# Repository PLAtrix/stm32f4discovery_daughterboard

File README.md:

This is a Daughterboard for the STM32F4 Discovery for Paparazzi.
Mainly a brakout board for all bus (UART, SPI, I2C...) and PWM outputs.

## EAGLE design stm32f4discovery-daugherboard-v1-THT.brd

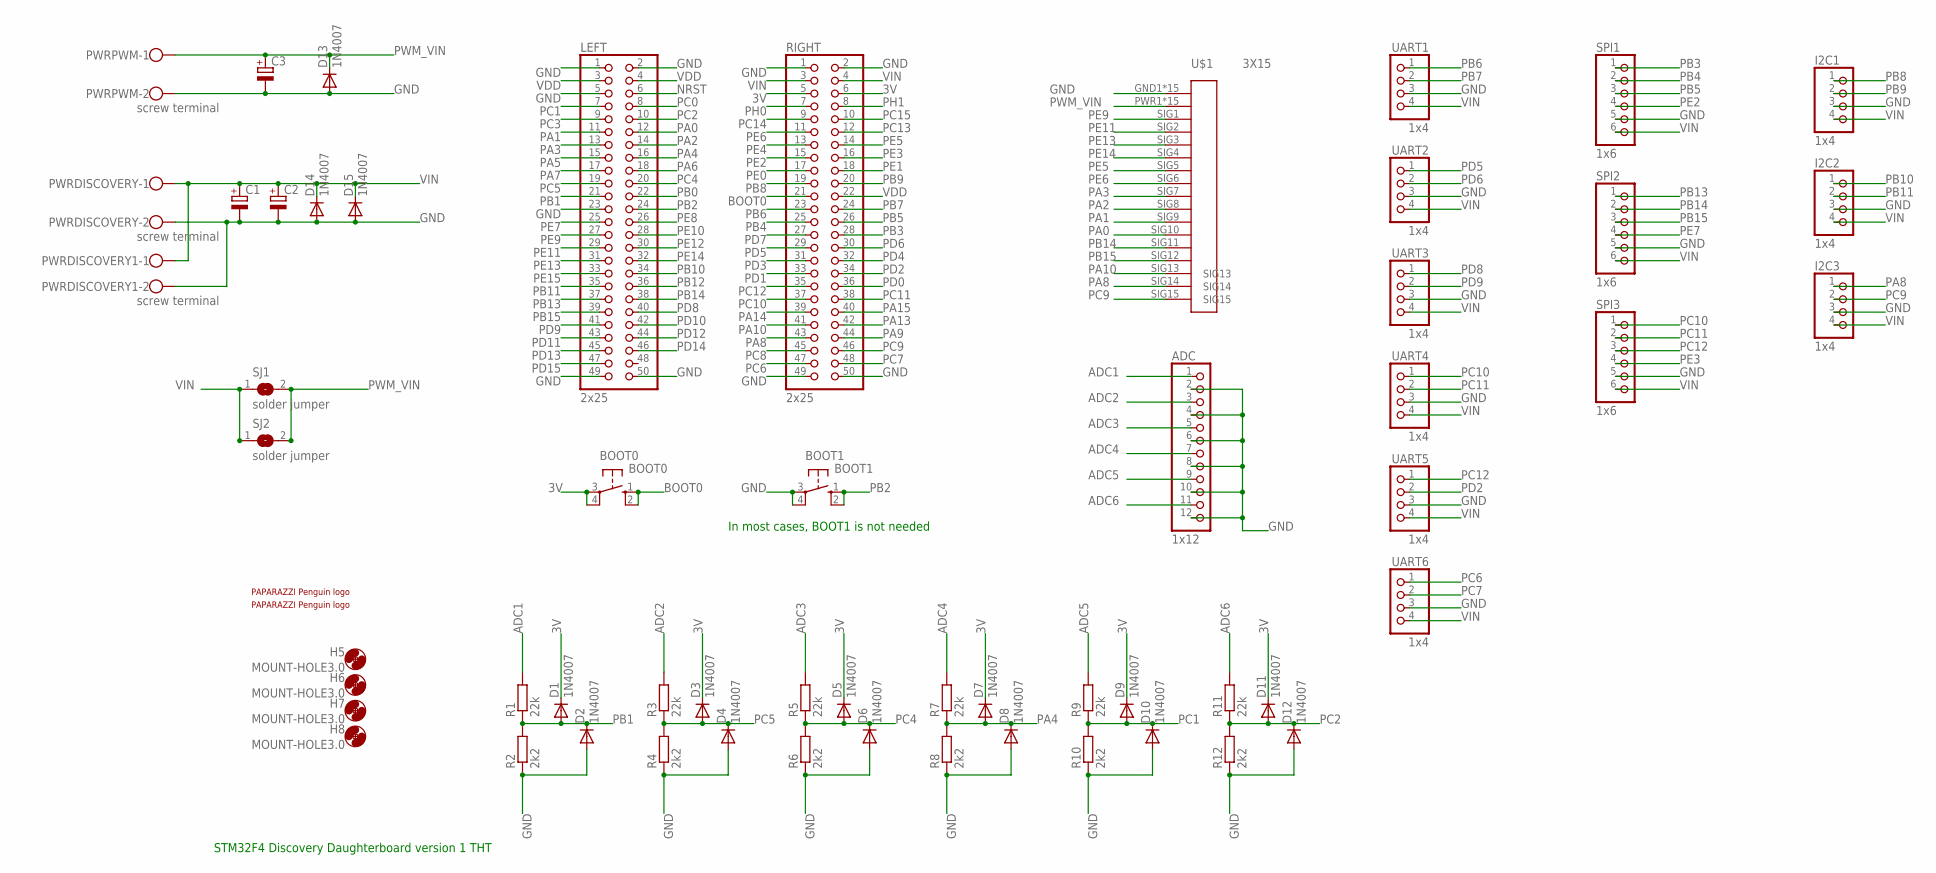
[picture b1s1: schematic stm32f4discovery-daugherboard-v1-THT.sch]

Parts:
ADC: 1x12; 1X12/90
BOOT0: BOOT0; B3F-10XX
BOOT1: BOOT1; B3F-10XX
C1, C2, C3: CPOL-EUE5-8.5; E5-8,5
D1, D2, D3, D4, D5, D6, D7, D8, D9, D10, D11, D12, D13, D14, D15: 1N4007; DO41-7.6_2
H5, H6, H7, H8: MOUNT-HOLE3.0; 3,0
I2C1, I2C2, I2C3: 1x4; 1X04/90
LEFT: 2x25; 2X25
PWRDISCOVERY: screw terminal; W237-102
PWRDISCOVERY1: screw terminal; W237-102; MPN 237-102
PWRPWM: screw terminal; W237-102
R1, R3, R5, R7, R9, R11: 22k; 0204/7
R2, R4, R6, R8, R10, R12: 2k2; 0204/7
RIGHT: 2x25; 2X25
SJ1, SJ2: solder jumper; SJW
SPI1, SPI2, SPI3: 1x6; 1X06/90
U$1: 3X15
U$2: PAPARAZZI
U$4: üAüARAZZI_1400; PAPARAZZI_1400
UART1, UART2, UART3, UART4, UART5, UART6: 1x4; 1X04/90

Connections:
3V: BOOT0.3, BOOT0.4 (P1), D1.C, D3.C, D5.C, D7.C, D9.C, D11.C, RIGHT.5, RIGHT.6
ADC1: ADC.1, R1.2
ADC2: ADC.3, R3.2
ADC3: ADC.5, R5.2
ADC4: ADC.7, R7.2
ADC5: ADC.9, R9.2
ADC6: ADC.11, R11.2
BOOT0: BOOT0.1 (S), BOOT0.2 (S1), RIGHT.21
GND: ADC.2, ADC.4, ADC.6, ADC.8, ADC.10, ADC.12, BOOT1.3, BOOT1.4 (P1), C1.-, C2.-, C3.-, D2.A, D4.A, D6.A, D8.A, D10.A, D12.A, D13.A, D14.A, D15.A, I2C1.3, I2C2.3, I2C3.3, LEFT.1, LEFT.2, LEFT.5, LEFT.23, LEFT.49, LEFT.50, PWRDISCOVERY.2, PWRDISCOVERY1.2, PWRPWM.2, R2.1, R4.1, R6.1, R8.1, R10.1, R12.1, RIGHT.1, RIGHT.2, RIGHT.49, RIGHT.50, SPI1.5, SPI2.5, SPI3.5, U$1.GND1 (GND), U$1.GND2 (GND), U$1.GND3 (GND), U$1.GND4 (GND), U$1.GND5 (GND), U$1.GND6 (GND), U$1.GND7 (GND), U$1.GND8 (GND), U$1.GND9 (GND), U$1.GND10 (GND), U$1.GND11 (GND), U$1.GND12 (GND), U$1.GND13 (GND), U$1.GND14 (GND), U$1.GND15 (GND), UART1.3, UART2.3, UART3.3, UART4.3, UART5.3, UART6.3
NRST: LEFT.6
PA0: LEFT.12, U$1.SIG10
PA1: LEFT.11, U$1.SIG9
PA2: LEFT.14, U$1.SIG8
PA3: LEFT.13, U$1.SIG7
PA4: D7.A, D8.C, LEFT.16, R7.1, R8.2
PA5: LEFT.15
PA6: LEFT.18
PA7: LEFT.17
PA8: I2C3.1, RIGHT.43, U$1.SIG14
PA9: RIGHT.44
PA10: RIGHT.41, U$1.SIG13
PA13: RIGHT.42
PA14: RIGHT.39
PA15: RIGHT.40
PB0: LEFT.22
PB1: D1.A, D2.C, LEFT.21, R1.1, R2.2
PB2: BOOT1.1 (S), BOOT1.2 (S1), LEFT.24
PB3: RIGHT.28, SPI1.1
PB4: RIGHT.25, SPI1.2
PB5: RIGHT.26, SPI1.3
PB6: RIGHT.23, UART1.1
PB7: RIGHT.24, UART1.2
PB8: I2C1.1, RIGHT.19
PB9: I2C1.2, RIGHT.20
PB10: I2C2.1, LEFT.34
PB11: I2C2.2, LEFT.35
PB12: LEFT.36
PB13: LEFT.37, SPI2.1
PB14: LEFT.38, SPI2.2, U$1.SIG11
PB15: LEFT.39, SPI2.3, U$1.SIG12
PC0: LEFT.8
PC1: D9.A, D10.C, LEFT.7, R9.1, R10.2
PC2: D11.A, D12.C, LEFT.10, R11.1, R12.2
PC3: LEFT.9
PC4: D5.A, D6.C, LEFT.20, R5.1, R6.2
PC5: D3.A, D4.C, LEFT.19, R3.1, R4.2
PC6: RIGHT.47, UART6.1
PC7: RIGHT.48, UART6.2
PC8: RIGHT.45
PC9: I2C3.2, RIGHT.46, U$1.SIG15
PC10: RIGHT.37, SPI3.1, UART4.1
PC11: RIGHT.38, SPI3.2, UART4.2
PC12: RIGHT.35, SPI3.3, UART5.1
PC13: RIGHT.12
PC14: RIGHT.9
PC15: RIGHT.10
PD0: RIGHT.36
PD1: RIGHT.33
PD2: RIGHT.34, UART5.2
PD3: RIGHT.31
PD4: RIGHT.32
PD5: RIGHT.29, UART2.1
PD6: RIGHT.30, UART2.2
PD7: RIGHT.27
PD8: LEFT.40, UART3.1
PD9: LEFT.41, UART3.2
PD10: LEFT.42
PD11: LEFT.43
PD12: LEFT.44
PD13: LEFT.45
PD14: LEFT.46
PD15: LEFT.47
PE0: RIGHT.17
PE1: RIGHT.18
PE2: RIGHT.15, SPI1.4
PE3: RIGHT.16, SPI3.4
PE4: RIGHT.13
PE5: RIGHT.14, U$1.SIG5
PE6: RIGHT.11, U$1.SIG6
PE7: LEFT.25, SPI2.4
PE8: LEFT.26
PE9: LEFT.27, U$1.SIG1
PE10: LEFT.28
PE11: LEFT.29, U$1.SIG2
PE12: LEFT.30
PE13: LEFT.31, U$1.SIG3
PE14: LEFT.32, U$1.SIG4
PE15: LEFT.33
PH0: RIGHT.7
PH1: RIGHT.8
PWM_VIN: C3.+, D13.C, PWRPWM.1, SJ1.2, SJ2.2, U$1.PWR1 (PWR), U$1.PWR2 (PWR), U$1.PWR3 (PWR), U$1.PWR4 (PWR), U$1.PWR5 (PWR), U$1.PWR6 (PWR), U$1.PWR7 (PWR), U$1.PWR8 (PWR), U$1.PWR9 (PWR), U$1.PWR10 (PWR), U$1.PWR11 (PWR), U$1.PWR12 (PWR), U$1.PWR13 (PWR), U$1.PWR14 (PWR), U$1.PWR15 (PWR)
VDD: LEFT.3, LEFT.4, RIGHT.22
VIN: C1.+, C2.+, D14.C, D15.C, I2C1.4, I2C2.4, I2C3.4, PWRDISCOVERY.1, PWRDISCOVERY1.1, RIGHT.3, RIGHT.4, SJ1.1, SJ2.1, SPI1.6, SPI2.6, SPI3.6, UART1.4, UART2.4, UART3.4, UART4.4, UART5.4, UART6.4

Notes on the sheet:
STM32F4 Discovery Daughterboard version 1 THT
In most cases, BOOT1 is not needed

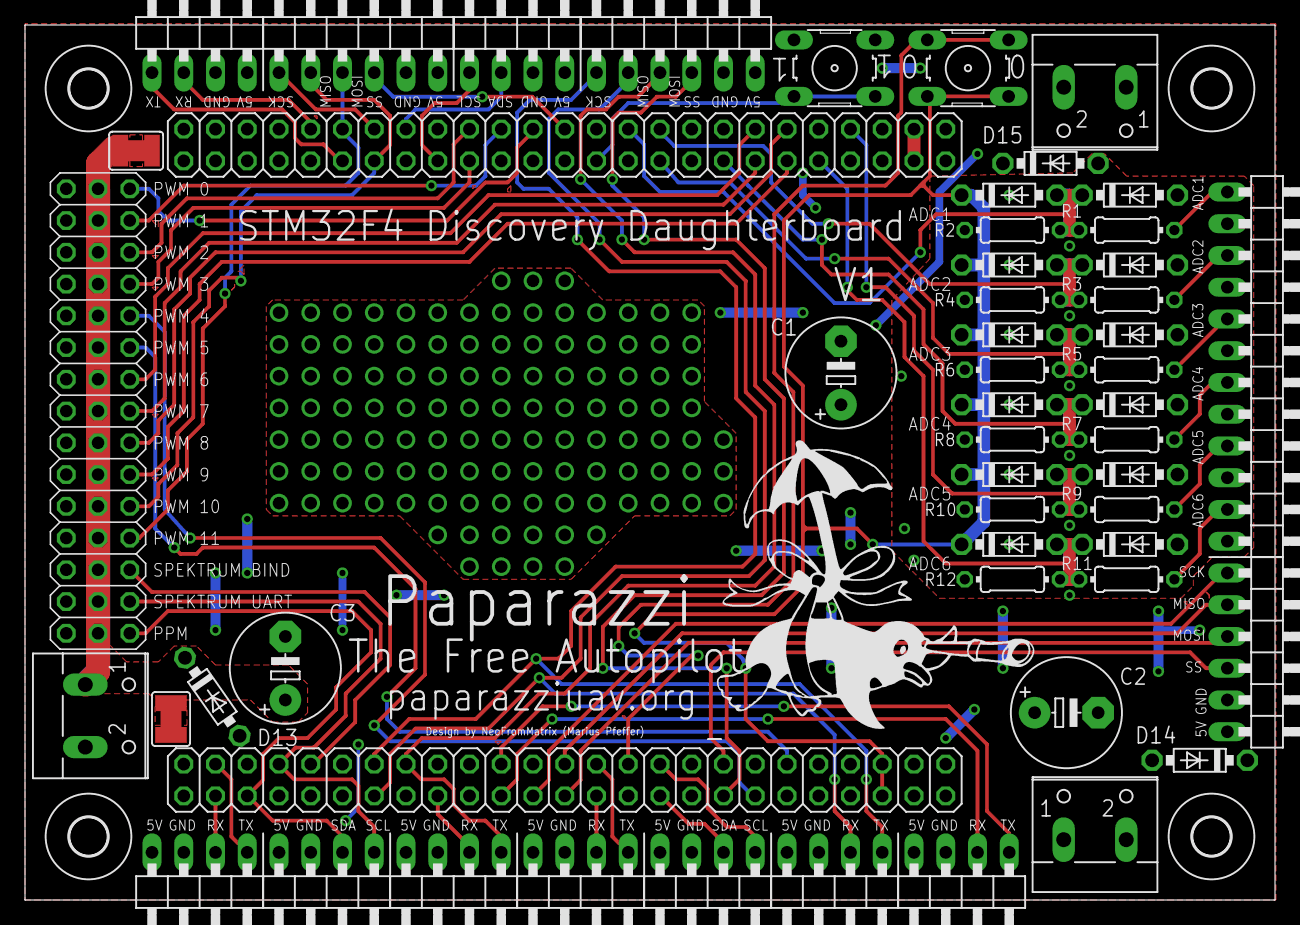
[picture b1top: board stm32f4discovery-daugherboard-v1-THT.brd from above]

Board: 2 copper layers, 100.0 x 70.0 mm, 59 parts (1 on the bottom side), 57 nets.

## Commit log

2014-03-13 initial push
2014-03-13 small improvements
2014-03-14 added v1 to name
2014-03-15 added version 2
2014-03-16 updated v2
2014-03-16 sikscreen
    sikscreen, paparazzi logo, prototyping are
2014-03-17 replaced v1 with v2
    deleted v1, renamed v2 to v1
2014-03-17 small changes
2014-03-17 minor edit
2014-03-17 corrected adc voltage divider
2014-03-18 added suppressor diode on all adc
2014-03-19 added tht version (without suppressor diodes)
2014-03-19 all tht components, adc input protection with diodes
2014-03-20 input protection
2014-03-22 deleted old version, small changes in tht version
2014-03-22 minor edits
2014-04-02 changed to kicad
2014-04-02 added pdf
2014-04-03 added gerber
    only first version, cleanup is required
2014-04-03 added pdf
    wrong trace with on pdf !
2014-04-07 added filter caps on input
2014-04-11 final v1.0
